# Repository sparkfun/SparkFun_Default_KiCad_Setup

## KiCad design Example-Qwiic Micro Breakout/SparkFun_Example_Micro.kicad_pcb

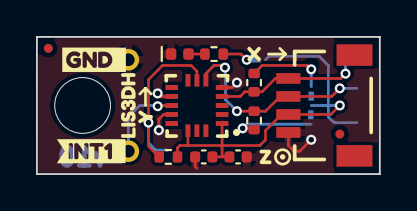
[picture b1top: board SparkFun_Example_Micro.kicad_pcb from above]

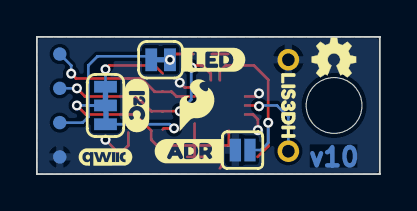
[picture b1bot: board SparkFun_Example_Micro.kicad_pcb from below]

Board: 2 copper layers, 19.0 x 7.6 mm, 33 parts (12 on the bottom side), 10 nets.

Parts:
C3: 0.1uF; C_0402_1005Metric
C4: 10uF; C_0402_1005Metric
D1: Red; LED_0402_1005Metric_Red
FID3, FID4: Fiducial_0.5mm; Fiducial_0.5mm_Mask1mm
G4: OSHW_Logo; Creative_Commons_License
J1, J5: PTH_1x1mm; 1x01_P2.0mm
J2: Qwiic_RA; JST_1x04_P1.0mm_Horizontal_SMD
JP1: LED; Jumper_2_NC_Trace
JP2: I2C; Jumper_3_NC-2_Trace
JP3: ADR; Jumper_2_NO
R1, R6: 2.2k; R_0402_1005Metric
R2: 10k; R_0402_1005Metric
R3: 4.7k; R_0402_1005Metric
Ref**: Val**; OSHW_Logo_2.5mm
ST1: Standoff
TP5, TP6, TP7, TP8: 0.75mm; TestPoint-0.75mm
U1: LIS3DH; ST_LGA-16_3x3mm_P0.5mm_5x3
kibuzzard-689A65D0: G***; kibuzzard-689A65D0
kibuzzard-689A65DA: G***; kibuzzard-689A65DA
kibuzzard-689A65F1: G***; kibuzzard-689A65F1
kibuzzard-689A65FB: G***; kibuzzard-689A65FB
kibuzzard-689A660E: G***; kibuzzard-689A660E
kibuzzard-689A665F: G***; kibuzzard-689A665F
kibuzzard-689A6605: G***; kibuzzard-689A6605
kibuzzard-689A6665: G***; kibuzzard-689A6665
kibuzzard-689A6668: G***; kibuzzard-689A6668
kibuzzard-689A6672: G***; kibuzzard-689A6672

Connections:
3.3V: C3.1, C4.1, J2.2, JP1.2 (B), JP2.2 (B), R2.2, TP7.1, U1.1 (VDDIO), U1.14 (VDD)
ADR/SDO: JP3.2 (B), R2.1, U1.7 (SA0/SDO)
GND: C3.2, C4.2, D1.1 (K), J2.1, J5.1, JP3.1 (A), TP8.1, U1.5 (GND), U1.10 (RES), U1.12 (GND)
INT1: J1.1, U1.11 (INT1)
unnamed: D1.2 (A), R3.2
unnamed: JP1.1 (A), R3.1
unnamed: JP2.1 (A), R6.2
unnamed: JP2.3 (C), R1.2
SCL: J2.4, R6.1, TP5.1, U1.4 (SCL/SPC)
SDA: J2.3, R1.1, TP6.1, U1.6 (SDA/SDI)

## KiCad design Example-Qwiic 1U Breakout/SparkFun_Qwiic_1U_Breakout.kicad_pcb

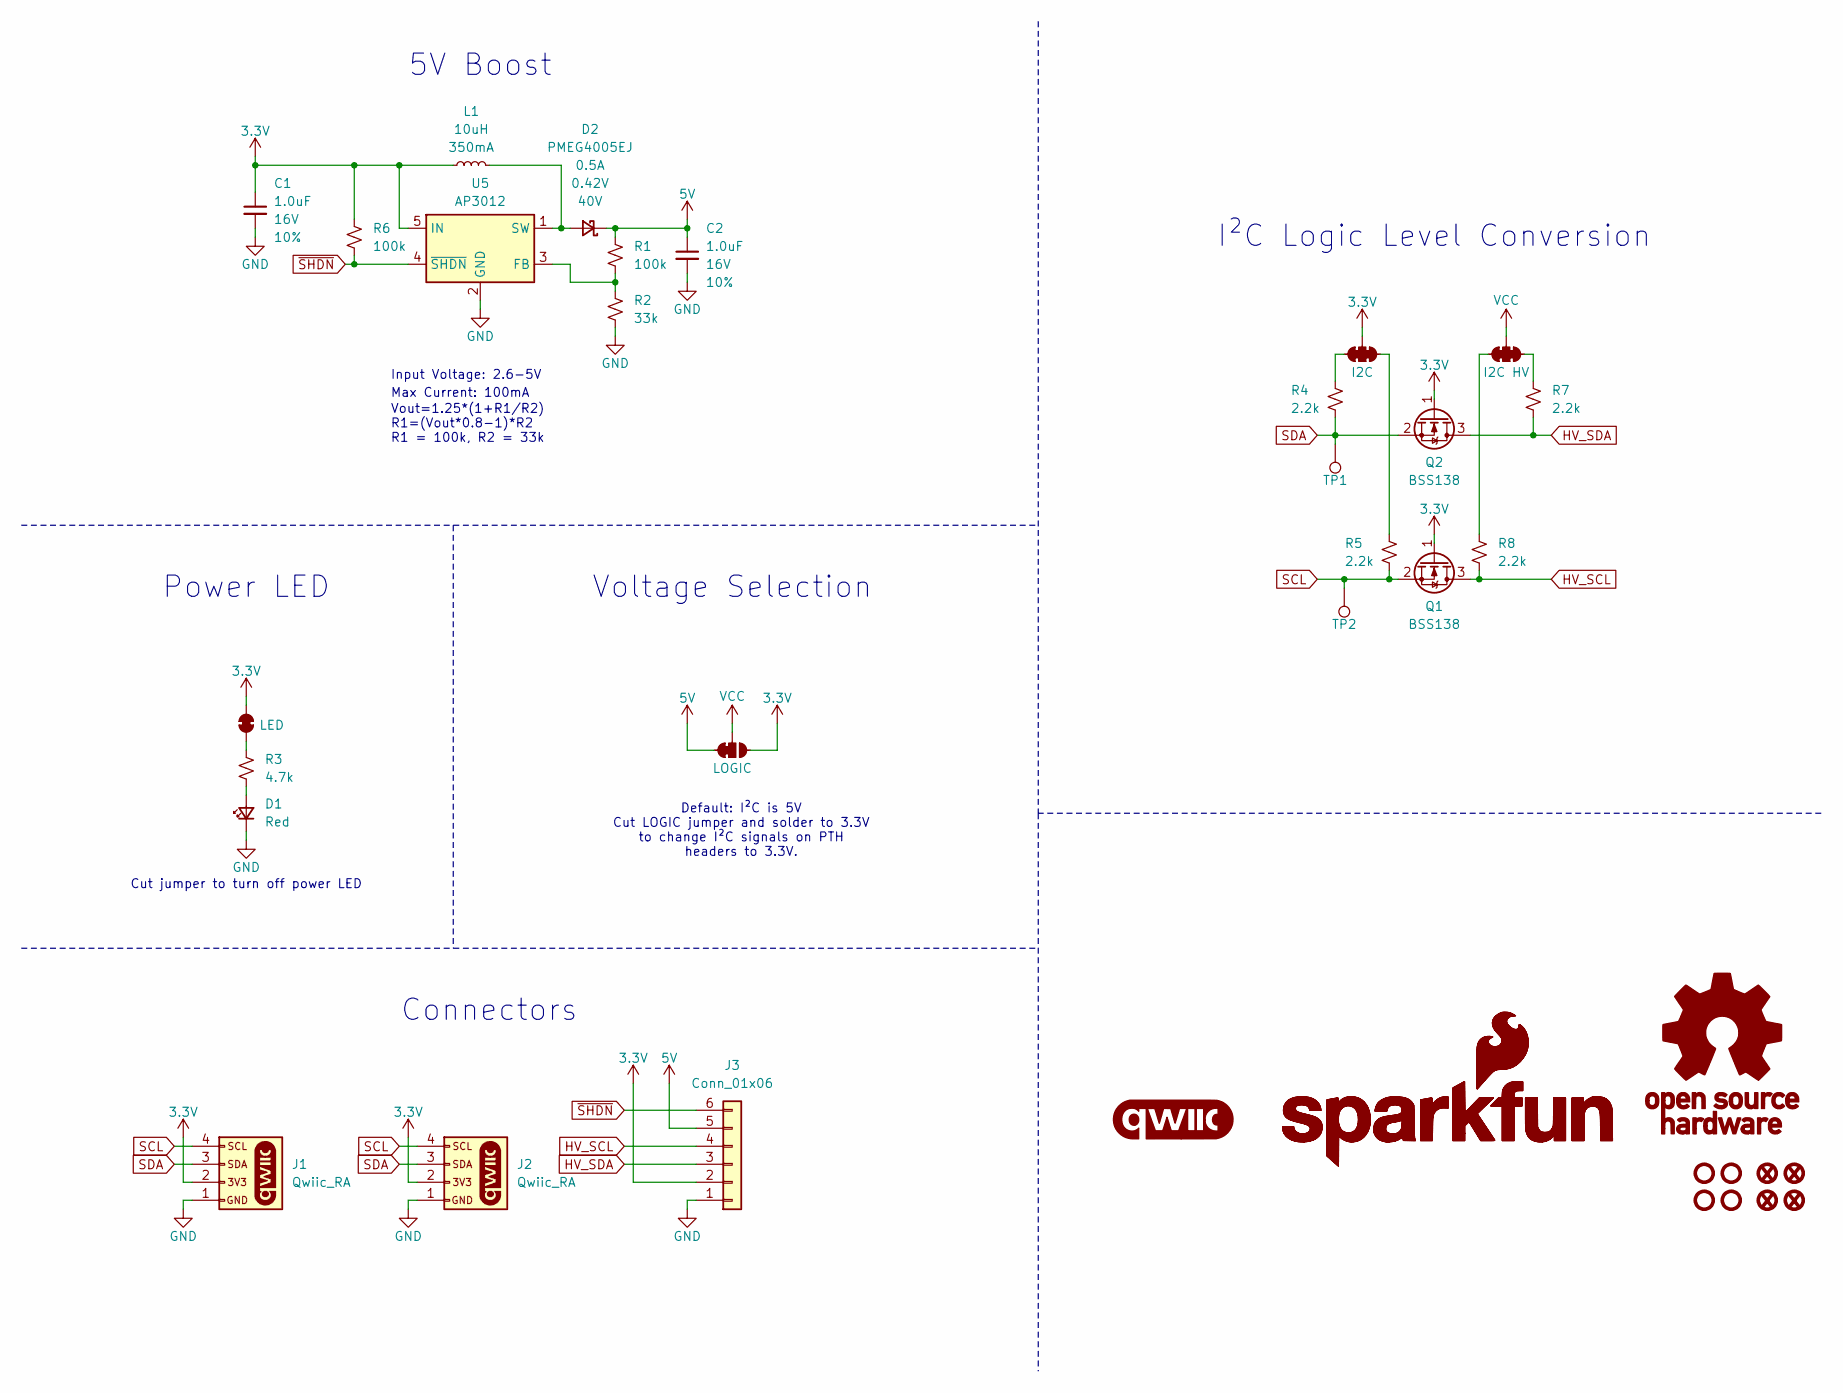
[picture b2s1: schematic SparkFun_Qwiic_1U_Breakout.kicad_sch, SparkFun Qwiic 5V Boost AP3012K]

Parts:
C1, C2: 1.0uF; C_0603_1608Metric; Voltage 16V; Tolerance 10%
D1: Red; LED_0603_1608Metric_Red
D2: PMEG4005EJ; SOD-323
FID1, FID2, FID3, FID4: Fiducial_0.5mm; Fiducial_0.5mm_Mask1mm
G1: qwiic_Logo
G2: SparkFun_Logo; SparkFun_Logo_8mm
G3: SparkFun_Logo
G4: OSHW_Logo; Creative_Commons_License
J1, J2: Qwiic_RA; JST_1x04_P1.0mm_Horizontal_SMD
J3: Conn_01x06; 1x06_P2.54mm
JP1: LED; Jumper_2_NC_Trace
JP2: I2C; Jumper_3_NC-2_Trace
JP3: LOGIC; Jumper_3_NC-1_Trace
JP4: I2C HV; Jumper_3_NC-2_Trace
L1: 10uH; C_0805_2012Metric
Q1, Q2: BSS138; SOT23-3
R1, R6: 100k; R_0603_1608Metric
R2: 33k; R_0603_1608Metric
R3: 4.7k; R_0603_1608Metric
R4, R5, R7, R8: 2.2k; R_0603_1608Metric
ST1, ST2, ST3, ST4: Standoff
TP1, TP2: 1.0mm; TestPoint-1.0mm
U5: AP3012; SOT23-5

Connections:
3.3V: C1.1, J1.2, J2.2, J3.2, JP1.2 (B), JP2.2 (B), JP3.3 (C), L1.1, Q1.1 (G), Q2.1 (G), R6.2, U5.5 (IN)
5V: C2.1, D2.1 (K), J3.5, JP3.1 (A), R1.2
GND: C1.2, C2.2, D1.1 (K), J1.1, J2.1, J3.1, R2.2, U5.2 (GND)
HV_SCL: J3.4, Q1.3 (D), R8.2
HV_SDA: J3.3, Q2.3 (D), R7.2
unnamed: D1.2 (A), R3.1
unnamed: D2.2 (A), L1.2, U5.1 (SW)
unnamed: JP1.1 (A), R3.2
unnamed: JP2.1 (A), R5.1
unnamed: JP2.3 (C), R4.2
unnamed: JP4.1 (A), R7.1
unnamed: JP4.3 (C), R8.1
unnamed: R1.1, R2.1, U5.3 (FB)
SCL: J1.4, J2.4, Q1.2 (S), R5.2, TP2.1
SDA: J1.3, J2.3, Q2.2 (S), R4.1, TP1.1
VCC: JP3.2 (B), JP4.2 (B)
~SHDN: J3.6, R6.1, U5.4 (~SHDN)

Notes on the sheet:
Input Voltage: 2.6-5V
Vout=1.25*(1+R1/R2) R1=(Vout*0.8-1)*R2 R1 = 100k, R2 = 33k
Default: I²C is 5V Cut LOGIC jumper and solder to 3.3V to change I²C signals on PTH headers to 3.3V.
I²C Logic Level Conversion
Max Current: 100mA
Cut jumper to turn off power LED
Power LED
Connectors
5V Boost
Voltage Selection

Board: 2 copper layers, 63 parts (26 on the bottom side), 17 nets, no tracks yet.

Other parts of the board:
kibuzzard-689A64A8: G***; kibuzzard-689A64A8
kibuzzard-689A66E2: G***; kibuzzard-689A66E2
kibuzzard-689A66E9: G***; kibuzzard-689A66E9
kibuzzard-689A66EE: G***; kibuzzard-689A66EE
kibuzzard-689A66F4: G***; kibuzzard-689A66F4
kibuzzard-689A66F9: G***; kibuzzard-689A66F9
kibuzzard-689A66FE: G***; kibuzzard-689A66FE
kibuzzard-689A642E: G***; kibuzzard-689A642E
kibuzzard-689A644B: G***; kibuzzard-689A644B
kibuzzard-689A648B: G***; kibuzzard-689A648B
kibuzzard-689A649F: G***; kibuzzard-689A649F
kibuzzard-689A670C: G***; kibuzzard-689A670C
kibuzzard-689A676B: G***; kibuzzard-689A676B
kibuzzard-689A6411: G***; kibuzzard-689A6411
kibuzzard-689A6418: G***; kibuzzard-689A6418
kibuzzard-689A6454: G***; kibuzzard-689A6454
kibuzzard-689A6479: G***; kibuzzard-689A6479
kibuzzard-689A6481: G***; kibuzzard-689A6481
kibuzzard-689A6494: G***; kibuzzard-689A6494
kibuzzard-689A6706: G***; kibuzzard-689A6706
kibuzzard-689A6711: G***; kibuzzard-689A6711
kibuzzard-689A6718: G***; kibuzzard-689A6718
kibuzzard-689A6721: G***; kibuzzard-689A6721
kibuzzard-689A6728: G***; kibuzzard-689A6728
kibuzzard-689A6759: G***; kibuzzard-689A6759
kibuzzard-689A6762: G***; kibuzzard-689A6762
kibuzzard-689A6771: G***; kibuzzard-689A6771
kibuzzard-689A6775: G***; kibuzzard-689A6775
kibuzzard-689A6796: G***; kibuzzard-689A6796

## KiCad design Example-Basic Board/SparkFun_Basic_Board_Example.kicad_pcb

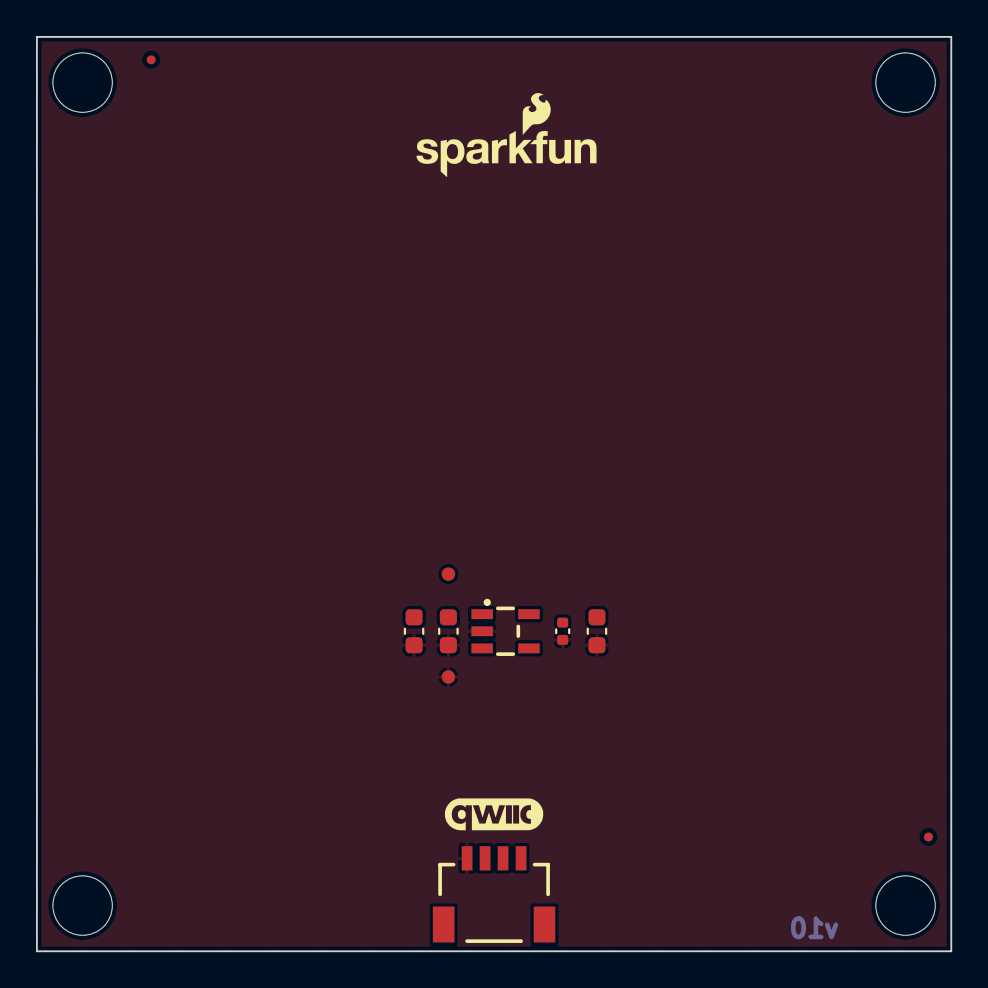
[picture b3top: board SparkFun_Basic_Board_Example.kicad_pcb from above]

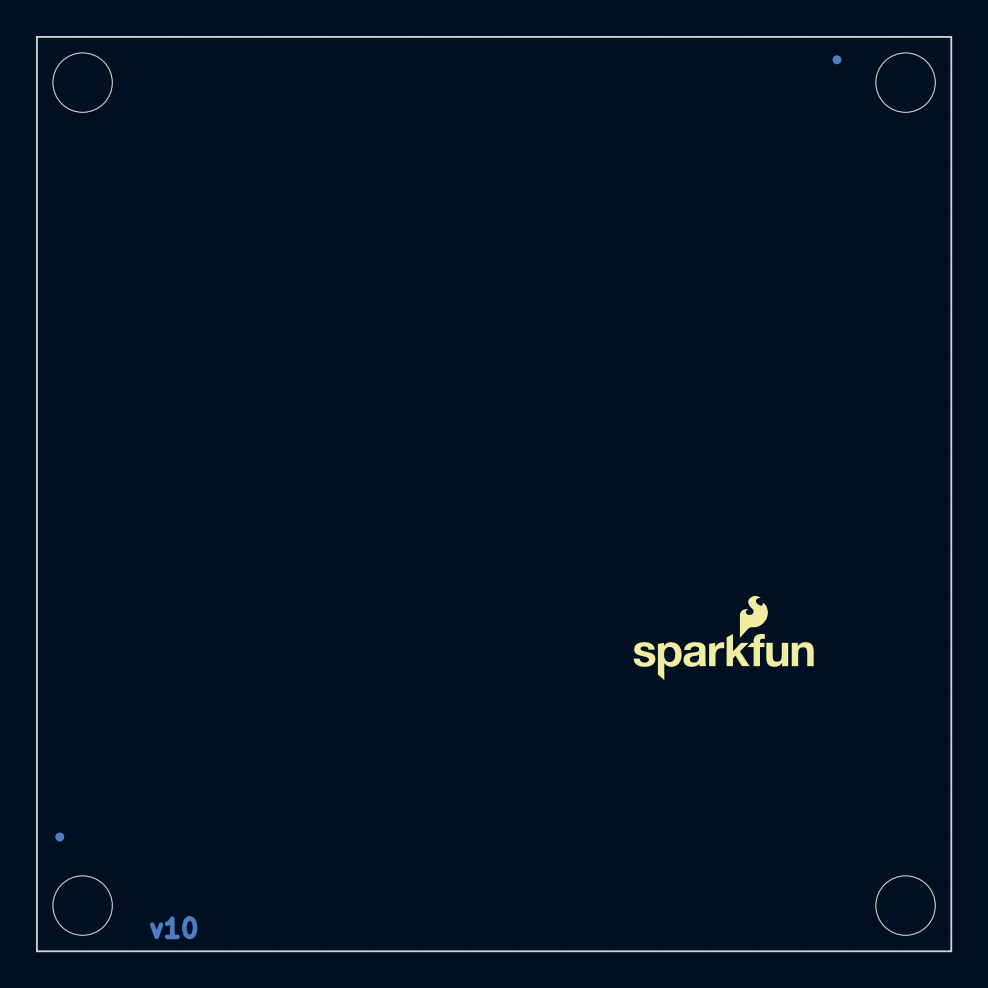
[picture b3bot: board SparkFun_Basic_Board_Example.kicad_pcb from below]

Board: 4 copper layers, 50.8 x 50.8 mm, 17 parts (2 on the bottom side), 3 nets, no tracks yet.

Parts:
C2, C5: 10uF; C_0603_1608Metric
C3: 1.0uF; C_0603_1608Metric
C4: 1.0uF; C_0402_1005Metric
FID1, FID2, FID3, FID4: Fiducial_0.5mm; Fiducial_0.5mm_Mask1mm
G3: OSHW_Logo; Creative_Commons_License
J1: Qwiic_RA; JST_1x04_P1.0mm_Horizontal_SMD
ST1, ST2, ST3, ST4: Stand_off; Standoff
TP1, TP2: TestPoint_0.75mm; TestPoint-0.75mm
U2: RT9080-3.3; SOT23-5

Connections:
3.3V: C4.1, C5.1, J1.2, U2.5 (VOUT)
GND: C2.2, C3.2, C4.2, C5.2, J1.1, TP1.1, U2.2 (GND)
VCC: C2.1, C3.1, TP2.1, U2.1 (VIN), U2.3 (EN)

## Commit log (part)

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2023-09-13 Change default net classes.
2023-11-13 Remove backup files
2023-11-19 Add dimensions
2023-11-19 Add copper weight
2023-11-19 Add readme and images
2024-01-15 Update fiducial symbol
2024-01-18 Add inner/outer copper weights
2024-01-18 Increase board edge DRC constraint to 10mil.
2024-01-19 Extend ignore for KiCad files
2024-01-19 Add silkscreen color to ordering instructions
2024-01-21 Remove islands from polygon.
2024-02-20 Remove SCH from ignore
2024-02-20 Update parts to new naming scheme
2024-03-06 Add basic regulator circuit to show various components
2024-03-06 Removing ordering instruction from SCH. Adding notes to PCB.
2024-03-06 Remove ordering instruction symbol from sch.
2024-03-06 Change page size and board origin
2024-03-06 Add title box defaults.
2024-08-12 Update to v8. Update soldermask color.
2024-08-23 Set pad_to_mask_clearance to 0.05mm
2024-09-26 Ignore sym-lib-table
2024-10-09 Update page settings
2025-02-03 Layer rename
2025-02-04 Fix typo in stackup
2025-02-13 Add schematic blocks
2025-02-19 Remove extra corners from GND polygon
2025-02-19 Add Qwiic connector and logos
    These are commonly needed, IMO should be part of the default setup
2025-02-21 Update material default to TG135
2025-03-18 Move examples into sub folder. Add 1U example.
2025-03-18 Modify copper to edge constraint
2025-03-26 Add hotkeys file
2025-04-11 Update examples to KiCad v9
2025-04-15 Rename Basic Board folder
2025-06-09 Adds Default Micro Setup
2025-06-20 Add Qwiic Micro example
2025-06-20 Remove duplicate files
2025-06-21 Add axis labels
2025-08-11 Make text gray. Superscript 2s. Add company name.
2025-08-11 Make labels fit standard
2025-08-11 Make labels and text follow standard
2025-11-08 Update examples with latest parts

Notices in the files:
parts and their libraries:
https://creativecommons.org/licenses/by-sa/4.0
Released under the Creative Commons Attribution Share-Alike 4.0 License
